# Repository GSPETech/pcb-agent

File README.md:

# PCB Agent

**Deterministic AI-powered PCB design harness for Diode/Zener toolchain.**

Vendor-neutral Python harness that coordinates schematic design, layout generation, and routing verification. AI agents may edit source files within policy boundaries, but **never decide verification truth or fabrication approval**—all gates are decided by locked TestBenches and evidence-backed adapters.

---

## Quick Start

### CLI Usage

```bash
# Verify existing project
./pcb-agent verify --project fixtures/valid-blinky --profile schematic

# Check toolchain and dependencies
./pcb-agent doctor --project fixtures/valid-blinky --format json

# Full layout workflow (schematic → placement → routing → DRC)
./pcb-agent verify --project my_board --profile layout
```

### AI Orchestrator (MCP)

Design PCBs end-to-end with one command:

```bash
/pcb_agent "buat schematic GPS tracker dengan IMU sensor"
```

Orchestrator automatically:
- Creates schematic with components and nets
- Generates layout with deterministic placement
- Routes traces via Freerouting
- Fixes DRC violations iteratively
- Returns `PASS` when all gates green

See [MCP Integration](#mcp-integration) for setup.

---

## Installation

**Requirements:** Python 3.11+, [Diode toolchain](https://github.com/diodeinc/pcb) 0.4.40+, KiCad 10.x (for layout profile)

### Standard

```bash
git clone https://github.com/GSPETech/pcb-agent
cd pcb-agent
python -m pip install -e .
```

Core has **zero third-party Python dependencies**. MCP server requires `mcp` package.

### Windows

```powershell
python pcb-agent doctor --project fixtures/valid-blinky --format json
```

**Note:** Layout profile requires WSL2 or Developer Mode (symlink privilege). Windows-native `pcb build` hits `os error 1314` without it.

---

## Commands

| Command | Purpose | Example |
|---------|---------|---------|
| `doctor` | Probe toolchain & dependencies | `./pcb-agent doctor --project . --format json` |
| `verify` | Run verification gates | `./pcb-agent verify --project . --profile layout` |
| `build` | Build Diode project | `./pcb-agent build --project .` |
| `check` | Run TestBenches | `./pcb-agent check --project .` |
| `layout` | Generate KiCad PCB | `./pcb-agent layout --project .` |
| `drc` | Run KiCad DRC | `./pcb-agent drc --project .` |
| `report` | Generate verification report | `./pcb-agent report --project .` |
| `run` | Delegate to AI backend | `./pcb-agent run --backend command "fix connectivity"` |

All external commands are capability-probed before execution. Netlist export, autorouting, Gerber generation, manufacturing, and ordering are intentionally absent.

---

## Verification Profiles

### `schematic`
Gates: `CONTRACT` → `DIODE_BUILD` → `CONNECTIVITY` → `SPECIFICATION`

Validates component topology, net connectivity, and spec constraints (value, package, pullup) via locked TestBenches. No layout or physical checks.

### `layout`
Gates: (all schematic) → `LAYOUT_GENERATE` → `PLACEMENT` → `ROUTE` → `LAYOUT_SYNC` → `KICAD_DRC`

Runs full physical design flow:
1. **LAYOUT_GENERATE**: `pcb layout` creates `.kicad_pcb` with footprints at origin
2. **PLACEMENT**: Deterministic component placement + Edge.Cuts outline derivation
3. **ROUTE**: Freerouting DSN/SES round-trip via `pcbnew` Python binding
4. **LAYOUT_SYNC**: `pcb layout --check` verifies sync between Zener and KiCad
5. **KICAD_DRC**: `kicad-cli pcb drc` validates manufacturing rules

Missing KiCad or Freerouting → `BLOCKED`. SPICE deferred to future release.

---

## Deterministic Verification

### Core Principle

**AI agents propose. Locked TestBenches decide.**

`CONNECTIVITY` and `SPECIFICATION` gates are decided exclusively by generated TestBenches that the harness owns and hashes. Agents may edit `src/`, `modules/`, `components/`, but **never** contracts (`SPEC.json`, `ACCEPTANCE.json`, `expected-connectivity.json`) or locked TestBenches (`tests/*.zen`).

### Adapter Registry

Component kinds (`resistor`, `led`, `capacitor`, etc.) are resolved through a **versioned adapter registry** keyed by:
- Component kind
- Verified `pcbc` versions (currently `0.4.40`)
- SHA-256 evidence hash from captured Diode runs
- Property accessors (`value`, `package`)
- Pull-up pin pairs (e.g., `["anode", "cathode"]`)

Registry validated lazily against `tests/evidence/diode-0.4.40/manifest.sha256` on first use. **Validation fails closed**—missing or mismatched evidence → `BLOCKED`.

**Registered kinds:** `resistor`, `led`, `capacitor`, `inductor`, `ferrite_bead`, `thermistor`, `zener`, `rectifier`, `tvs`

**Intentionally absent:** Crystal (adapter model cannot represent 1→4 GND pin mapping). ICs, connectors, switches (no verified adapters yet).

### Evidence Chain

Every verification run records:
1. Generated TestBench source + SHA-256
2. Raw `pcb test` JSON result + SHA-256
3. Command metadata (sanitized paths, durations)
4. Immutable safety fields (`production_ready: false`, `fabrication_approved: false`)

Gates digest evidence bytes, not stdout. `result_sha256` attests the exact input that produced the verdict.

### Gate Rules

- **Status vocabulary:** `PASS` | `FAIL` | `BLOCKED` | `SKIPPED`
- **Fail-closed:** Unsupported kind, unverified toolchain version, malformed evidence → `BLOCKED`
- **Exact reconciliation:** `total` = record count, `passed` + `failed` = `total`
- **No silent pass:** Every `value`/`package` constraint must emit an assertion or report `BLOCKED`
- **Topology verification:** `required_pullup` checks exact net membership, not just name existence
- **Dependency cascade:** Failed/blocked prerequisite → dependents `BLOCKED`, never `FAIL`

See `AGENT_PROTOCOL.md` for full contract semantics.

---

## Exit Codes

| Status | Exit | Meaning |
|--------|-----:|---------|
| `PASS` | 0 | All required gates passed |
| `FAIL` | 1 | Deterministic validation failed (design mismatch) |
| `BLOCKED` | 2 | Dependency/toolchain/evidence unavailable |
| Invalid input | 3 | Contract/configuration malformed |
| Backend crash | 4 | Timeout, no-progress, iteration limit |
| `HUMAN_REVIEW` | 5 | Explicit human decision required |

`human_review_required: true` in report does **not** force exit 5. Every report keeps `production_ready: false` and `fabrication_approved: false` regardless of gate status.

---

## MCP Integration

### Setup

1. **Install MCP server:**
```bash
cd ~/.agents/mcp-servers
git clone https://github.com/GSPETech/pcb-agent pcb-agent-mcp
cd pcb-agent-mcp
pip install -e .
```

2. **Register in `opencode.json`:**
```json
{
  "mcpServers": {
    "pcb-agent": {
      "command": "python",
      "args": ["-m", "pcb_agent.mcp_server"],
      "env": {
        "PCB_AGENT_ROOT": "/path/to/pcb-agent"
      }
    }
  }
}
```

3. **Add CLI command:**
```bash
# ~/.claude/commands/pcb_agent.sh
#!/bin/bash
TASK="$1"
PROJECT_DIR="${2:-$(pwd)/pcb_project}"

opencode tool call pcb-agent pcb_design \
  --task "$TASK" \
  --project_dir "$PROJECT_DIR" \
  --profile full
```

### Usage

```bash
# Full workflow
/pcb_agent "buat GPS tracker dengan IMU sensor"

# Schematic only
/pcb_agent "buat schematic power supply 5V" --profile schematic

# Repair specific gate
/pcb_agent repair KICAD_DRC --project ./my_board
```

**Exposed tools:**
- `pcb_design` — orchestrate schematic → layout → routing
- `pcb_verify` — run verification gates
- `pcb_repair` — fix specific gate failure with loop detection

### Agent Flow

```
user: /pcb_agent "buat GPS tracker"
  ↓
MCP pcb_design tool
  ↓
orchestrator.py
  ├→ schematic_agent
  │   └→ repair loop (max 5 iter) → PASS
  ├→ layout_agent
  │   └→ repair loop (max 5 iter) → PASS
  └→ routing_agent
      └→ DRC fix loop (max 10 iter) → PASS
  ↓
return: {
  "status": "PASS",
  "summary": "Schematic PASS (2 iter), Layout PASS (3 iter), DRC PASS (7 violations fixed)",
  "files_created": ["src/gps_module.zen", "tests/gps_test.zen"]
}
```

---

## Reports

Runs write structured reports to `reports/<run-id>/`:
- `verify-report.json` — full verification result with evidence hashes
- `summary.md` — human-readable gate status + durations
- `raw/` — captured evidence (TestBench source, JSON results, DRC output)

Reports include:
- ✓ Check statuses with durations
- ✓ Sanitized command metadata (no absolute home paths)
- ✓ SHA-256 hashes for all generated/captured artifacts
- ✓ Git worktree status (dirty allowed, reported when available)
- ✓ Immutable safety fields (`production_ready: false`, `fabrication_approved: false`)

**Note:** Symlink to `reports/` in project root → writes outside workspace. See security findings.

---

## AI Backends

Generic command backend:
- Reads TOML argv array from config
- Transports task via stdin or literal argv (no shell interpolation)
- Limited to 5 attempts per `run` invocation
- Rejects nested `PCB_AGENT_ACTIVE` (no backend-spawns-backend)
- Protects contracts and locked TestBenches (hash-verified, denied in edit allowlist)
- Detects no-progress via fingerprint comparison
- Independently invokes `verify` after each edit

**Codex adapter:** Probes `codex exec --help` only; invocation disabled until version flags verified.

**Repository skill:** `agents/openai.yaml` intentionally `BLOCKED`—no consumer format verified.

---

## Security Boundary

### Workspace Isolation
- ✓ Executables inside workspace rejected
- ✓ CWD and all file ops must stay in canonical workspace
- ✓ Protected files hashed and snapshotted before backend runs
- ✓ Trusted TestBenches run from harness-owned evidence copy

### Process Containment
- ✓ Child environment allowlisted (no `LD_PRELOAD`, `PYTHONPATH`)
- ✓ Secrets redacted from logs (`sk-`, `ghp_`, `xoxb-`, private keys, JWT)
- ✓ stdout/stderr bounded (no DOS via infinite output)

### Network Policy
- ✗ **Network deny is assertion-only, no OS-level sandbox**
- ⚠ MVP: only fake/local backends should be configured until enforcement exists

### Absent by Design
- No `sudo` or privilege escalation
- No installer execution
- No recursive cleanup beyond `reports/`
- No autorouter, manufacturing, or ordering actions

### Known Issues
See [Security Findings](#security-findings) for active vulnerabilities (S1-S10).

---

## Project Structure

### Required Files (project root)
```
project.toml              # profile, source, test, [toolchain], [layout]
SPEC.json                 # requirements with constraints
ACCEPTANCE.json           # checks mapping requirements
expected-connectivity.json # components, nets, design rules
tests/<name>.zen          # locked TestBench (name matches ACCEPTANCE.checks[].test)
```

Templates: `skill/diode-pcb-agent/assets/project-template/`

### Supported Layouts
1. **Fixture layout:** `src/board.zen` entry point
2. **Board repository:** `.zen` files at root, subcircuits in `modules/` and `components/`

Both produce identical snapshot for verification (`src/**`, `modules/**`, `components/**`, `*.zen`, `pcb.toml`, `pcb-version`).

### Naming Rules

Net and component ref names must match `[A-Za-z][A-Za-z0-9_-]*` (rendered into Zener source). Hierarchical refs use dot separator (`IMU.R17`, `POWER.C1`).

**Common violations from `pcb import`:**
| Import name | Normalized |
|-------------|------------|
| `+3_3V` | `VDD_3V3` |
| `IMU_XTAL+` | `IMU_XTAL_P` |
| `Net-(U1-VOUT)` | `NET_U1_VOUT` |
| `/IMU/BNO_SCL` | `IMU_BNO_SCL` |

Rename **only** spelling; topology and net membership unchanged.

---

## Toolchain Requirements

### Diode
- **Version:** 0.4.40 (adapter registry pinned)
- **Install:** `pcb toolchain install 0.4.40`
- **Verify:** `pcb --version`

**Pin version in project:**
```bash
mkdir -p /tmp/pcbshim
printf '#!/bin/bash\nexec "$HOME/.local/bin/pcb" +0.4.40 "$@"\n' > /tmp/pcbshim/pcb
chmod +x /tmp/pcbshim/pcb
export PATH="/tmp/pcbshim:$PATH"
```

**Known issue:** Registry rejects 0.4.41+ → `BLOCKED`. Re-capture evidence or accept lane-range (future work).

### KiCad (layout profile only)
- **Version:** 10.x (10.0.3, 10.0.5 verified)
- **Required:**
  - `kicad-cli` in `PATH`
  - `pcbnew` Python binding for DSN/SES conversion
- **Verify:**
```bash
kicad-cli version
python3 -c "import pcbnew; print(pcbnew.GetBuildVersion())"
```

### Freerouting (layout profile only)
- **Version:** 2.3.0
- **Verify:** `freerouting --help`
- **Determinism:** Verified byte-identical SES output on identical DSN input

Missing `kicad-cli`, `pcbnew`, or `freerouting` → gates `BLOCKED`, not `FAIL`.

---

## Development

### Tests
```bash
python -m pytest -q          # 304 pass / 19 skip
python -m pyright            # clean
```

**CI:** `.github/workflows/ci.yml` runs pytest on ubuntu+windows × py3.11/3.13, pyright ubuntu/3.11 only.

**Known gaps:**
- `tests/` not typechecked (pyright `include=["src"]`)
- No lint job (no ruff/black config)
- 19 Windows skips cover security-critical symlink/traversal checks

### Before Commit
```bash
python -m pytest -q
python -m pyright
git diff --check  # catch trailing whitespace
```

Never commit:
- Archives, board deliverables, `reports/` runs
- Scratch exports (`*.zip`, `*.tar.gz`, `diodeinc_scratch_*/`)
- Secrets (`.env`, `credentials.json`, private keys)

### Branch Strategy
- `master` — stable
- `feat/*` — features
- `fix/*` — bug fixes

Always push to feature branch, never directly to `master`. Use `gh pr create` for PRs.

---

## Security Findings

| ID | Severity | Issue | Location |
|----|----------|-------|----------|
| S1 | High | `reports/` symlink writes outside workspace | `state.py:70-73` |
| S2 | High | `trusted_executable_roots` never passed → any PATH exe accepted | `process.py:103` |
| S3 | Medium | Symlink check after `resolve()` always False (no-op) | `kicad.py:18-19` |
| S4 | High | `src/**` snapshot follows symlinks despite `allow_symlinks=false` | `diode.py:264,332` |
| S5 | Low | Absolute home paths in reports violate attestation portability | `process.py:117` |
| S6 | High | Env passes `HOME`/`USERPROFILE` → child reads `~/.pcb` creds | `process.py:19` |
| S7 | Critical | Backend guard is env var check, one `export` from bypass | `backends/command.py:34` |
| S8 | Medium | Secret redaction misses `xoxb-`, `-----BEGIN PRIVATE KEY-----`, JWT | `process.py:22-26` |
| S9 | **Critical** | `.git` eligible for `unlink()` in restore → repo corruption | `cli.py:413-423` |
| S10 | High | Pre-existing symlinks unlinked, never restored | `cli.py:426-429` |

**S9/S10 are destructive.** Fix before any backend run on real repo.

---

## Correctness Findings

- Windows lock never reclaimable: `os.kill(pid,0)` raises `OSError [WinError 87]`, not `ProcessLookupError` → stale lock forever (`policy.py:33-37`)
- `BLOCKED` ranked above `FAIL` → contradicts `AGENT_PROTOCOL.md:76` (`models.py:50-56`)
- `HUMAN_REVIEW` never emitted (`human_review_required` hardcoded `True`) → exit 5 dead (`models.py:16,93`)
- `PathViolation` (ValueError subclass) → exit 4, contract says 3 (`cli.py:634,692`)
- Status vocab split: generated checks accept `PASS|PASSED|OK`, locked acceptance demands `"pass"` (`diode.py:130` vs `:248`)
- Fingerprint hashes only status+message → two different compile errors identical → premature exit 4 (`cli.py:447`)
- `configured_command` validates literals it wrote, reads nothing from `project.toml` (`diode.py:55-72`)

---

## Known Limitations

### Design
- **No fabrication approval:** `PASS` ≠ production-ready. Human review required.
- **Component coverage:** Only 9 passive kinds. ICs, connectors, switches absent.
- **Crystal support:** Blocked by 1→4 GND pin mapping (adapter model limitation).
- **MPN verification:** No verified accessor → always `BLOCKED`.
- **SPICE:** Deferred to future release.

### Toolchain
- **Version pin fragile:** Adapter registry rejects 0.4.41+ → weekly upstream releases break harness.
- **Upstream supersedes harness:** `diodeinc/pcb` now ships `skills/`, `pcb dfm`, `pcb sync`, `pcb toolchain pin`—harness reimplements worse.
- **No lane-range support:** Must re-capture 148-entry evidence bundle per patch release.

### Platform
- **Windows:** Layout profile requires WSL2 or Developer Mode (symlink privilege).
- **Determinism:** Freerouting verified deterministic; placement is deterministic; but no CI job enforces it.

---

## Integration Results

**Empirical run 2026-08-29 (Diode 0.4.40, WSL2):**
- ✓ `valid-blinky` → full `PASS`
- ✓ `invalid-syntax` → `DIODE_BUILD` `FAIL`
- ✓ `invalid-connectivity`, `invalid-value` → build `PASS`, locked test `FAIL`
- ✓ KiCad 10.0.5 DRC → exit 5 for 3 violations (harness mapped correctly)
- ✓ End-to-end layout harness → generated board, ran Diode layout check, ran KiCad JSON DRC
- ✗ Generated `valid-blinky` layout → `FAIL` (missing outline, 5 silkscreen warnings, 1 unconnected)

**Evidence:** `tests/evidence/diode-0.4.40/manifest.sha256` (148 entries), `docs/spike-diode-net-naming.md`

---

## Contributing

1. Read `AGENT_PROTOCOL.md` and `REVIEW_REMEDIATION_PLAN_V2.md`
2. Fix S9/S10 first (destructive paths)
3. Add tests for new gates/adapters
4. Capture evidence before registering new component kinds
5. Run `pytest` + `pyright` + `git diff --check` before commit
6. Never edit contracts, locked TestBenches, or evidence to make tests pass

---

## License

See `LICENSE` file.

---

## Fabrication Disclaimer

**Verification `PASS` does not mean production-ready.**

All reports carry `production_ready: false` and `fabrication_approved: false`. Fabrication requires:
- Human review by qualified engineer
- Physical inspection of generated layout
- Validation against design intent and requirements
- Sign-off before manufacturing

This harness validates adherence to contracts and design rules. It does **not** validate safety, functionality, or fitness for purpose.

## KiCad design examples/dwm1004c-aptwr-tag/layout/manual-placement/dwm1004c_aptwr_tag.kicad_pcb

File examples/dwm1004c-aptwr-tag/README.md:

# DWM1004C AP-TWR tag

A 72-component UWB tag board, migrated from an existing KiCad project into
Zener and verified with `pcb-agent`. It exists to show what the harness can and
cannot do on a real design, in one place that can be re-run.

Everything here was produced by the tools; nothing is hand-drawn.

## Layout

| Path | What it is |
|---|---|
| `dwm1004c_aptwr_tag.zen` | board entry point |
| `modules/` | `IMU`, `MAIN_MODULE_TAG`, `POWER` subcircuits |
| `components/` | 24 component packages, symbols, and 11 footprints |
| `SPEC.json`, `ACCEPTANCE.json`, `expected-connectivity.json` | harness contracts |
| `project.toml`, `pcb.toml` | project and workspace manifests |
| `tests/dwm_test.zen` | locked TestBench |
| `layout/agent-verified/` | KiCad output produced by the harness |
| `layout/dwm1004c_aptwr_tag/` | KiCad output from manual commands, for comparison |
| `migration-notes/` | reports and one-off scripts kept from the migration |

## Reproducing the verification

The adapter registry is pinned to `pcbc 0.4.40`, and `pcb.toml` only accepts a
lane, so pin the exact toolchain with a shim (see `AGENTS.md`):

```sh
pcb toolchain install 0.4.40
mkdir -p /tmp/pcbshim
printf '#!/bin/bash\nexec "$HOME/.local/bin/pcb" +0.4.40 "$@"\n' > /tmp/pcbshim/pcb
chmod +x /tmp/pcbshim/pcb
export PATH="/tmp/pcbshim:$PATH"

./pcb-agent verify --project examples/dwm1004c-aptwr-tag --profile schematic --format json
./pcb-agent verify --project examples/dwm1004c-aptwr-tag --profile layout --format json
```

The layout profile additionally needs `freerouting` and the `pcbnew` Python
bindings on `PATH`. Without them the `ROUTE` gate reports `BLOCKED`, not `FAIL`.

Run on Linux or WSL2: Windows-native `pcb build` fails with `os error 1314`.

## Recorded result

Schematic profile reaches `PASS` on all five required gates. Layout profile:

```
LAYOUT_GENERATE  PASS
PLACEMENT        PASS   placed 72 footprints; board 63.32 x 89.38 mm
ROUTE            PASS   routed 361 wires and 95 vias
LAYOUT_SYNC      FAIL
KICAD_DRC        FAIL   KiCad DRC found violations
```

The retained report is in `layout/agent-verified/verification/`.

`KICAD_DRC FAIL` is the correct outcome, not a defect in the gates. What the
placement and routing gates changed, measured on this board:

| | before | after |
|---|---:|---:|
| unconnected items | 169 | 6 |
| DRC violations | 285 | 72 |
| courtyard overlaps | 3 | 0 |
| tracks | 0 | 742 |

## Known limitations this board demonstrates

**Coverage is partial.** Only 47 of 72 components are declared in the
contracts, all resistors and capacitors. The rest — ICs, connectors, switches,
the crystal, LEDs, the inductor, the ferrite bead — are emitted by `pcb import`
as bespoke `Component()` with `type=None`, so no verified adapter describes
them. They cannot reach `PASS`; the harness reports `BLOCKED` rather than
guessing.

**59 DRC errors remain**, and they are intrinsic to two imported footprints, not
to placement: `S1` has a pad pitch that bridges its own solder mask, and the
`J3` USB-C footprint has a mask polygon overlapping its own pads. Fixing those
requires editing the footprints.

**The placer is grid-based.** It separates parts enough to route, which is what
it was built for. The board it produces is 63 × 89 mm against the original
50 × 40 mm, because it does not compact the way a human does. The comparison
folder `layout/dwm1004c_aptwr_tag/` uses placement transferred from the original
board and has 9 DRC errors instead of 59 — worth reading side by side.

**The layout profile does not emit `.kicad_sch`.** The schematic in
`layout/agent-verified/` came from a separate `pcb apply schematic` run.

## Not fabrication-ready

Every report carries `production_ready: false` and `fabrication_approved:
false`. Verification `PASS` means the declared contracts held, nothing more.
Fabrication needs review and approval by an engineer.

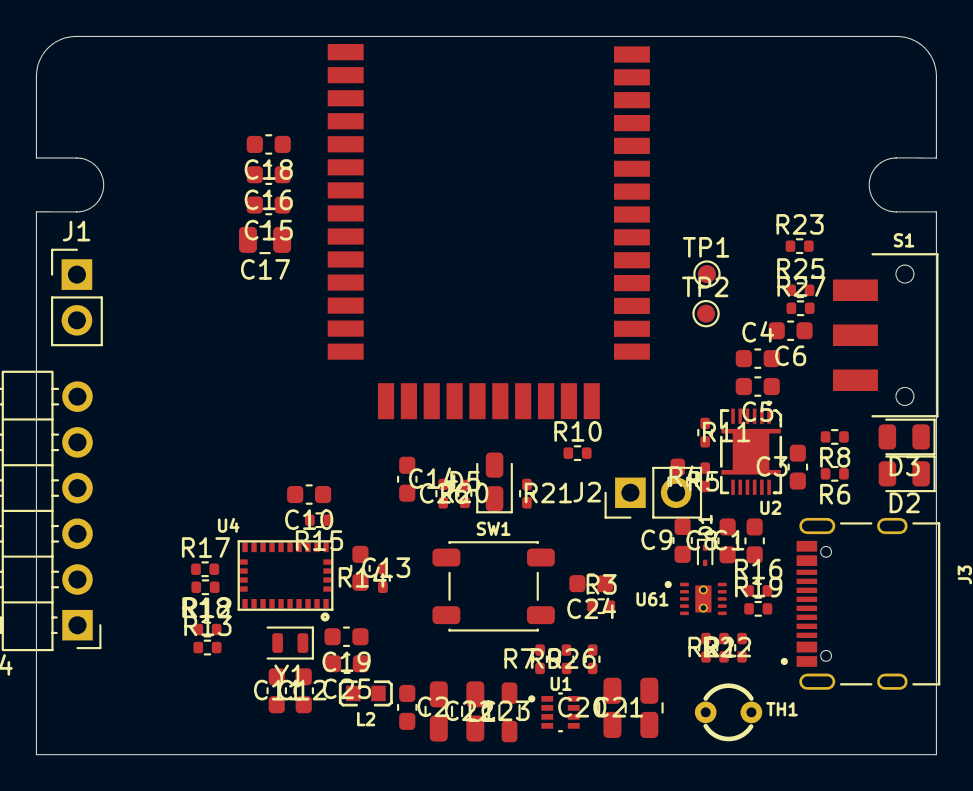
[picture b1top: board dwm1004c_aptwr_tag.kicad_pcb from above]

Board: 4 copper layers, 50.0 x 39.9 mm, 72 parts (1 on the bottom side), 46 nets, no tracks yet.

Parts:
C1, C4, C10, C24: 1uF; C_0603_1608Metric
C2, C3, C6, C8, C13, C14, C15, C16, C18, C19, C25: 100nF; C_0603_1608Metric
C5: 470nF; C_0603_1608Metric
C9: 10uF; C_0603_1608Metric
C11, C12: 22pF; C_0603_1608Metric
C17, C20, C21, C22, C23: 22uF; C_0805_2012Metric
C26: 100nF; C_0402_1005Metric
D1: ESD9B5.0ST5G; D_SOD-923
D2, D3, D5: KT; LED_0805_2012Metric
J1, J2: PZ254V; PinHeader_1x02_P2.54mm_Vertical
J3: TYPE; HRO_TYPE-C-31-M-12
J4: PZ254R; PinHeader_1x06_P2.54mm_Horizontal
L1: TFM201208ALD; L_0805_2012Metric
L2: BLM18PG121SN1D; L0603
R1: ERA; R_0402_1005Metric
R2: 18k; R_0402_1005Metric
R3, R4, R10, R11, R14, R15, R17, R18, R20, R25, R26: 10k; R_0402_1005Metric
R5: RL0603FR; R_0603_1608Metric
R6, R8: 1k; R_0402_1005Metric
R7: 511k; R_0402_1005Metric
R9: 91k; R_0402_1005Metric
R12, R13: 4.7k; R_0402_1005Metric
R16, R19: 5.1k; R_0402_1005Metric
R21: FRC0402F4700TS; R_0402_1005Metric
R22: ?; R_0402_1005Metric
R23, R27: 100k; R_0402_1005Metric
S1: JS102011SAQN; SW_JS102011SAQN
SW1: PTS 647 SN38 SMTR2 LFS; SW_SPST_PTS647_Sx38
TH1: MF52A103F3435; RES-TH_BD2.8_NTC-10K
TP1, TP2: ?; TestPoint_Pad_D1.0mm
U1: TPS631000DRLR; SOT50P160X60-8N
U2: BQ27441DRZR; SON-12_L4.0-W2.5-P0.40-BL-EP
U4: BNO055; LGA28R50P4X10_380X520X100
U51: DWM1004C
U61: BQ25185DLHR; IC_BQ25185DLHR
Y1: NX2012SA; Crystal_SMD_2012-2Pin_2.0x1.2mm

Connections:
GND: C1.2, C2.2, C3.2, C4.2, C5.1, C6.2, C8.2, C9.2, C10.2, C11.1, C12.2, C13.1, C14.2, C15.2, C16.2, C17.2, C18.2, C19.2, C20.2, C21.2, C22.2, C23.2, C24.2, C25.2, C26.2, D1.1, J2.2, J3.A1_B12, J3.B1_A12, J3.S1, J3.S2, J3.S3, J3.S4, J4.5, R1.1, R2.1, R3.1, R4.2, R9.2, R10.2, R16.1, R18.2, R19.1, R22.2, R23.2, R26.2, R27.1, S1.1, SW1.1, TH1.2, U1.7, U2.3, U2.13, U4.2, U4.5, U4.6, U4.18, U4.25, U51.GND@1, U51.GND@14, U51.GND@24, U51.GND@25, U51.GND@38, U61.5, U61.11, U61.12, U61.13
IMU.IMU_ADDR_SEL: R17.2, R18.1, U4.17
IMU.IMU_XTAL_N: C12.1, U4.26, Y1.2
IMU.IMU_XTAL_P: C11.2, U4.27, Y1.1
IMU.NET_U4_CAP: C10.1, U4.9
IMU.NET_U4_NBOOT_LOAD_PIN: R14.2, U4.4
IMU_BNO_SCL: R12.2, U2.2, U4.19, U51.SCL
IMU_BNO_SDA: R13.2, U2.1, U4.20, U51.SDA
IMU_IMU_INT: U4.14, U51.PA0
IMU_IMU_NRST: R15.2, U4.11, U51.PA1
MAIN_MODULE_TAG.MAIN_MODULE_TAG_CONFIG: C26.1, R20.2, SW1.2, U51.PB3
MAIN_MODULE_TAG.MAIN_MODULE_TAG_DWM_IND: R21.1, U51.PB5
MAIN_MODULE_TAG.MAIN_MODULE_TAG_DWM_RX1: J1.2, TP1.1, U51.RX
MAIN_MODULE_TAG.MAIN_MODULE_TAG_DWM_TX1: J1.1, TP2.1, U51.TX
MAIN_MODULE_TAG.MAIN_MODULE_TAG_MCU_BOOT: J4.1, R10.1, U51.MCU_BOOT
MAIN_MODULE_TAG.MAIN_MODULE_TAG_MCU_NRST: J4.2, U51.MCU_NRST
MAIN_MODULE_TAG.MAIN_MODULE_TAG_PA8: U51.INT2, U51.PA8
MAIN_MODULE_TAG.MAIN_MODULE_TAG_SWCLK: J4.3, U51.SWCLK
MAIN_MODULE_TAG.MAIN_MODULE_TAG_SWDIO: J4.4, U51.SWDIO
MAIN_MODULE_TAG.NET_D5_K: D5.1, R21.2
MAIN_MODULE_TAG.NET_R23_Pad1: R23.1, U51.PA4
POWER.NET_D2_A: D2.2, R6.1
POWER.NET_D3_A: D3.2, R8.1
POWER.NET_J3_CC1: J3.A5, R19.2
POWER.NET_J3_CC2: J3.B5, R16.2
POWER.NET_R25_Pad2: R25.2, S1.3
POWER.NET_U1_FB: R7.2, R9.1, U1.8
POWER.NET_U1_VOUT: C2.1, C22.1, C23.1, L2.1, R7.1, U1.1
POWER.NET_U2_VDD: C5.2, U2.5
POWER.NET_U6_CE: R3.2, U61.4
POWER.NET_U6_ILIM_VSET: R2.2, U61.7
POWER.NET_U6_ISET: R1.2, U61.8
POWER.NET_U6_TS_MR: R22.1, TH1.1, U61.6
POWER.POWER_BAT_P: C4.1, J2.1, R5.1, U2.6, U2.8
POWER.POWER_BIN: R4.1, U2.10
POWER.POWER_EN: C6.1, R27.2, S1.2, U1.5
POWER.POWER_LX1: L1.1, U1.3
POWER.POWER_LX2: L1.2, U1.2
POWER.POWER_MODE: R26.1, U1.6
POWER.POWER_SRN: C24.1, R5.2, U2.7, U61.2
POWER.POWER_STAT1: D3.1, U61.9
POWER.POWER_STAT2: D2.1, U61.3
POWER.VBUS: C1.1, C8.1, D1.2, J3.A4_B9, J3.B4_A9, U61.10
POWER.VCC: C9.1, C20.1, C21.1, R6.2, R8.2, R25.1, U1.4, U61.1
POWER_GPOUT: C3.1, R11.2, U2.12, U51.PB4
VDD_3V3: C13.2, C14.1, C15.1, C16.1, C17.1, C18.1, C19.1, C25.1, D5.2, J4.6, L2.2, R11.1, R12.1, R13.1, R14.1, R15.1, R17.1, R20.1, U4.3, U4.28, U51.VDDAON, U51.VDDIO, U51.VDD_DW, U51.VDD_MCU
